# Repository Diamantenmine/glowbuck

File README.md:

# glowbuck
Glowbuck is a voltage converter and control board that allows you to power addressable LED strips with USB-C PD.

Together with [Firefly Luciferin](https://github.com/sblantipodi/firefly_luciferin), you can create your own ambilight that connects via USB-C to your computer and draws power from a USB-C PD power supply. Glowbuck is in no way associated with the linked project.

The left USB-C socket is used for data. The right socket shall be connected to a suitable USB-C PD supply. The spring-loaded connection terminal allows easy and safe connection to a 5 V addressable LED strip with, for example, SK6812 or WS2812B. The output current is measured with a 2 mOhm shunt. A shunt amplifier allows the integrated ESP32 S3 to measure the current flow and shut down the buck regulator when an unusually large current is detected.

## Quick Facts:
- Output: 5 V @ 10 A
- Input: 20 V @ 3 A. Via I2C, the microcontroller can reconfigure the PD controller and negotiate other voltage and current requirements for the input.
- Microcontroller: ESP32 S3
- Output current measurement with an integrated shunt

## Warning and Disclaimer

**Warning**: This project is in a alpha state and the hardware has not yet been tested.

This project is provided "as is" without warranty of any kind, either expressed or implied. The author makes no guarantees regarding the functionality, reliability, or suitability of this project for any particular purpose.
By using this project, you acknowledge and agree that:
- No liability is accepted for any damages, losses, or issues arising from the use or inability to use this project
- There is no guarantee that this project will work as intended or work at all
- The author shall not be held responsible for any direct, indirect, incidental, or consequential damages

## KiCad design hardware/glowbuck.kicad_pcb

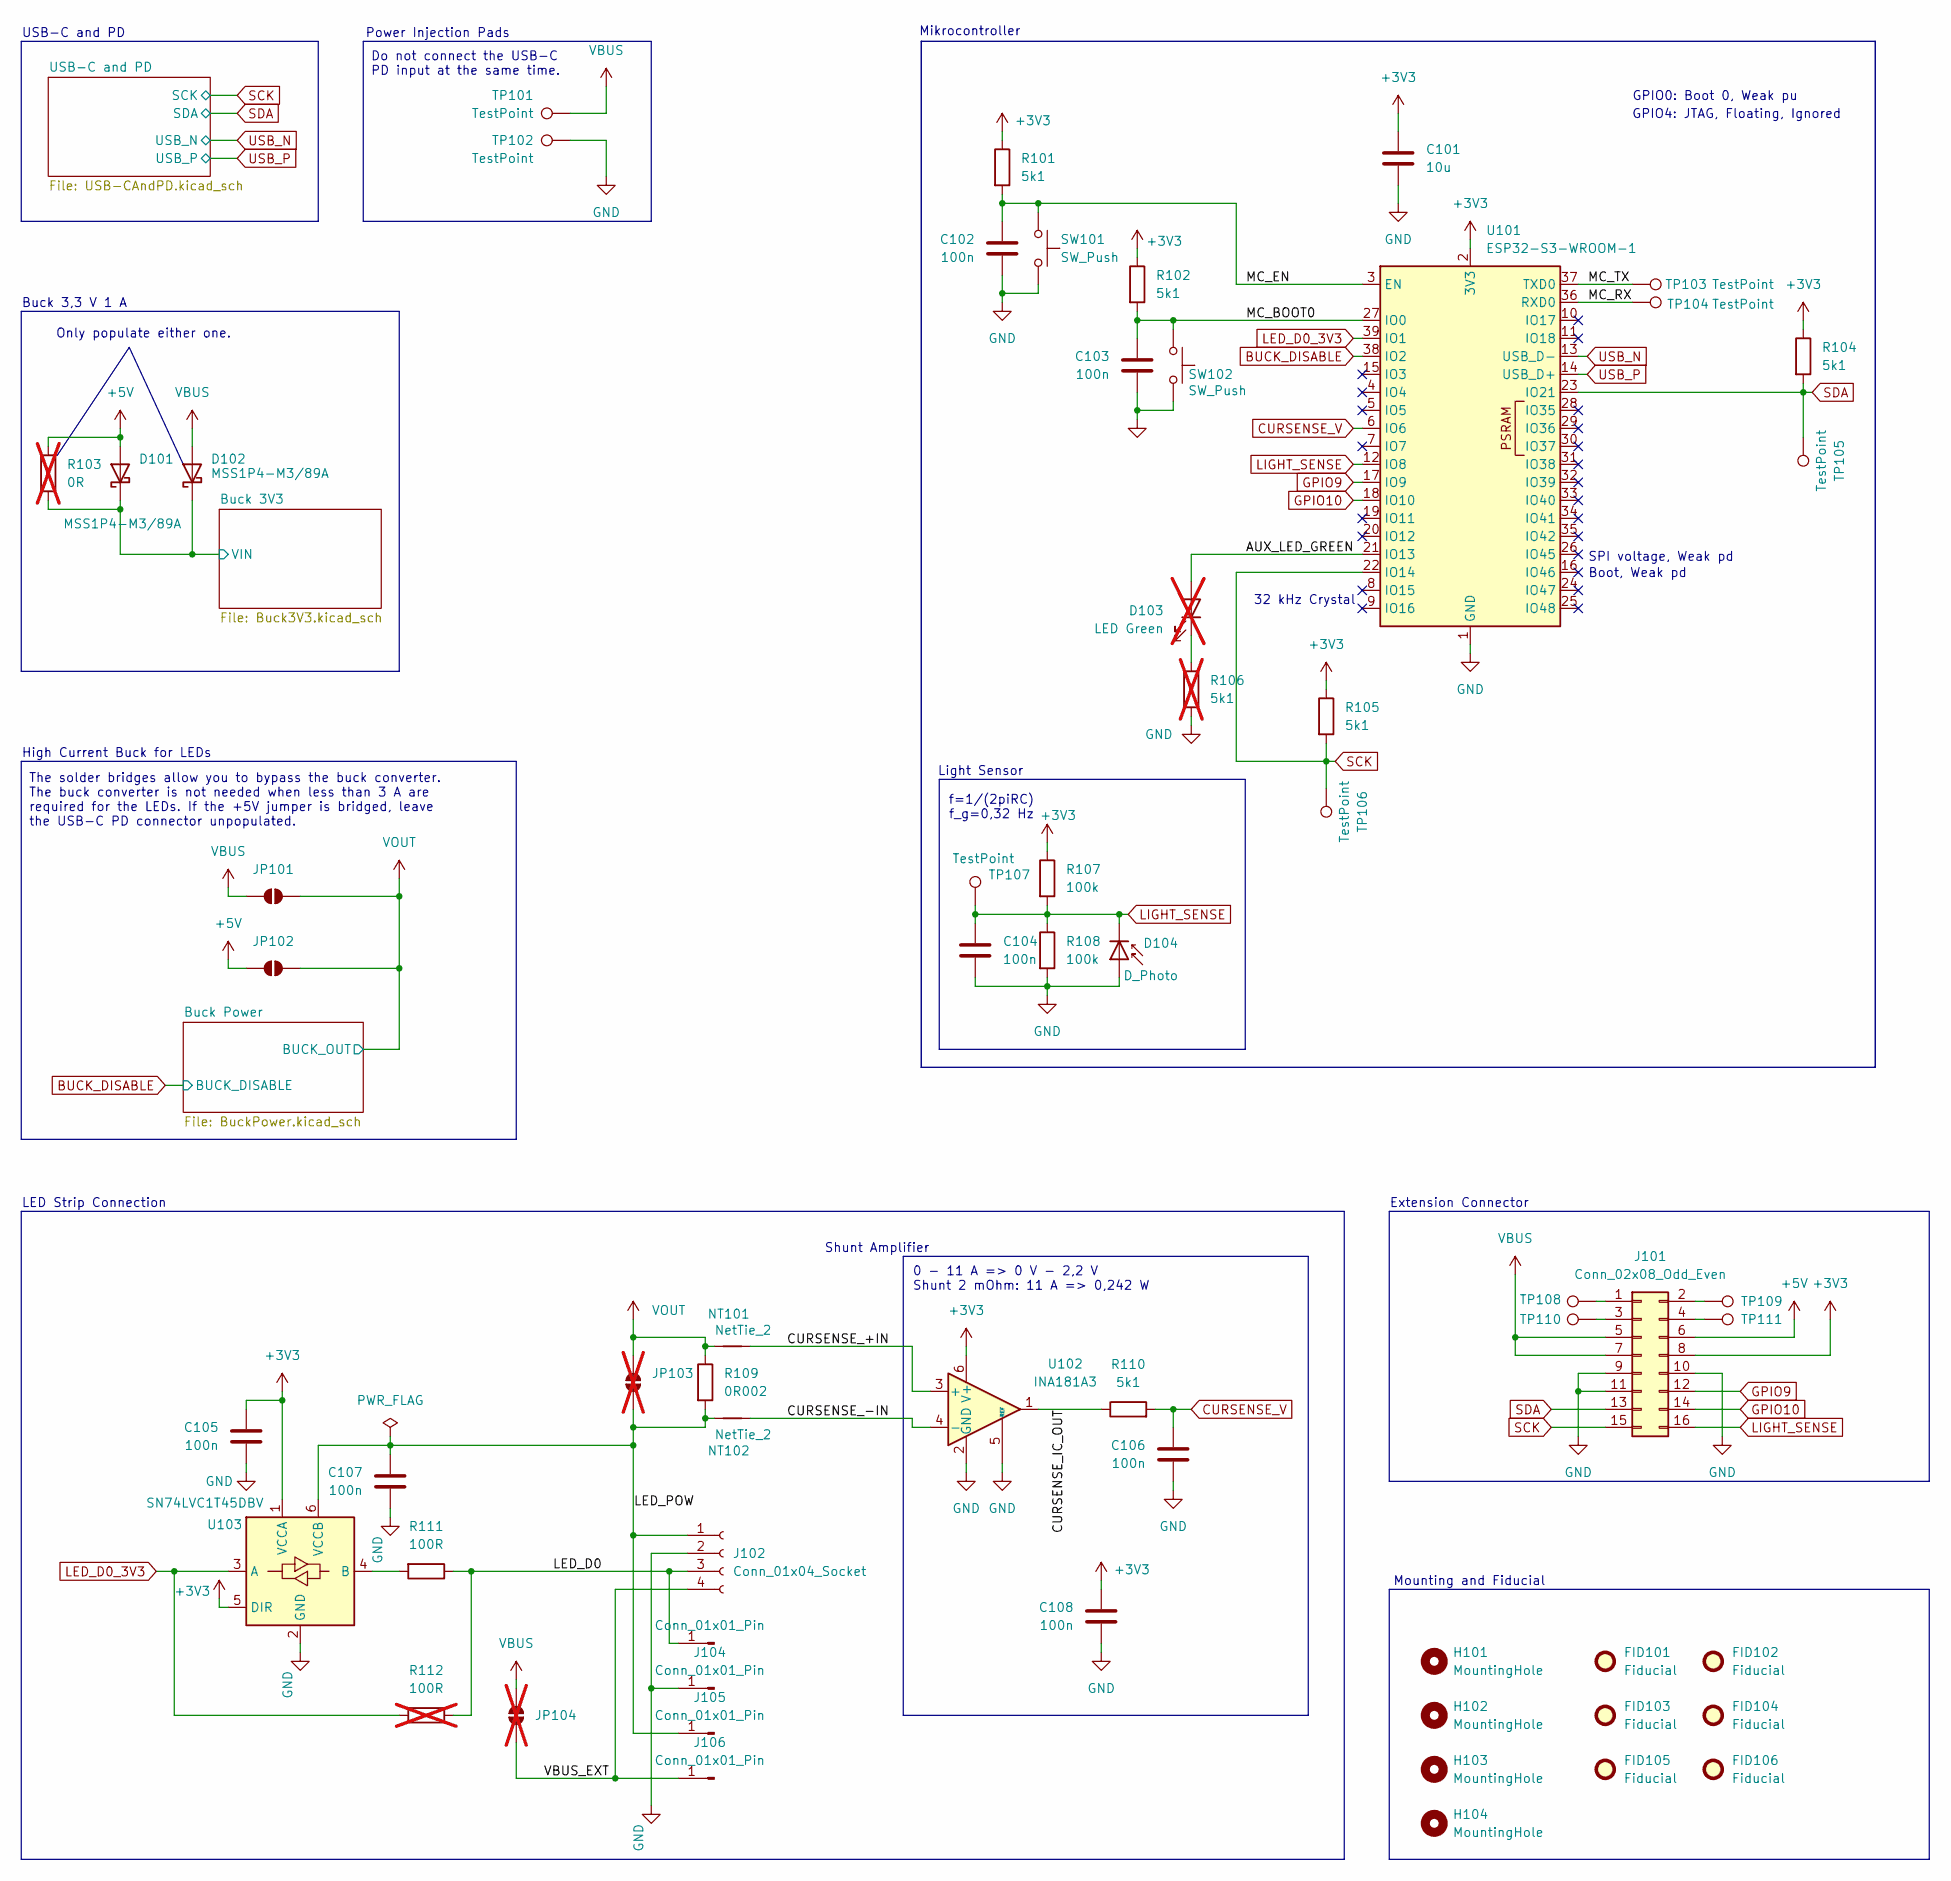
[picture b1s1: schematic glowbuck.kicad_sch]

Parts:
C101: 10u; C_0603_1608Metric; MouserNumber 187-CL10A106MA8NRNC
C102, C103, C104, C105, C106, C107, C108: 100n; C_0603_1608Metric; MouserNumber 187-CL10B104KB8WPND
D101, D102: MSS1P4-M3/89A; D_MicroSMP_AK; MouserNumber 625-MSS1P4-M3
D103: LED Green; LED_0603_1608Metric; MouserNumber 710-150060VS55040; not fitted
D104: D_Photo; D_1206_3216Metric; MouserNumber 743-IN-S126BTNPD
FID101, FID102, FID103, FID104, FID105, FID106: Fiducial; Fiducial_0.5mm_Mask1mm
H101, H102, H103, H104: MountingHole; MountingHole_2.2mm_M2_DIN965_Pad_TopBottom
J101: Conn_02x08_Odd_Even; PinHeader_2x08_P2.00mm_Vertical
J102: Conn_01x04_Socket; PTS 1,5_ 4-5,0-H; MouserNumber 651-1792889
J103: Conn_01x01_Pin; TestPoint_Pad_1.0x1.0mm
J104, J105, J106: Conn_01x01_Pin; TestPoint_Pad_3.0x3.0mm
JP101, JP102: SolderJumper_2_Open; SolderJumper_Open_HighCurrent
JP103, JP104: SolderJumper_2_Open; SolderJumper_Open_HighCurrent; not fitted
NT101, NT102: NetTie_2; NETTIE_0.3mm
R101, R102, R104, R105, R110: 5k1; R_0603_1608Metric; MouserNumber 603-RC0603FR-105K1L
R103: 0R; R_0603_1608Metric; MouserNumber 603-RC0603FR-130RL; not fitted
R106: 5k1; R_0603_1608Metric; MouserNumber 603-RC0603FR-105K1L; not fitted
R107, R108: 100k; R_0603_1608Metric; MouserNumber 603-RT0603FRE07100KL
R109: 0R002; R_0805_2012Metric; MouserNumber 71-WFC08052L000FE66
R111: 100R; R_0603_1608Metric; MouserNumber 603-RE0603FRE07100RL
R112: 100R; R_0603_1608Metric; MouserNumber 603-RE0603FRE07100RL; not fitted
SW101, SW102: SW_Push; PTS526_GPins_NoGround_2Pole; MouserNumber 611-PTS526SM20S21LFS
TP101, TP102: TestPoint; TestPoint_Pad_3.0x3.0mm
TP103, TP104, TP105, TP106, TP107, TP108, TP109, TP110, TP111: TestPoint; TestPoint_Pad_D1.0mm
U101: ESP32-S3-WROOM-1; MouserNumber 356-ESP32-S3WROOM1N4
U102: INA181A3; SOT-23-6; MouserNumber 595-INA181A3IDBVR
U103: SN74LVC1T45DBV; SOT-23-6; MouserNumber 595-74LVC1T45DBVRG4

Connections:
+3V3: C101.1, C105.1, C108.1, J101.8, R101.1, R102.1, R104.1, R105.1, R107.1, U101.2 (3V3), U102.6 (V+), U103.1 (VCCA), U103.5 (DIR); also elsewhere on the board
+5V: D101.2 (A), J101.6, JP102.1 (A), R103.2; also elsewhere on the board
/AUX_LED_GREEN: D103.2 (A), U101.21 (IO13)
/Buck 3V3/VIN: D101.1 (K), D102.1 (K), R103.1; also elsewhere on the board
/CURSENSE_+IN: NT101.1, U102.3 (+)
/CURSENSE_-IN: NT102.1, U102.4 (-)
/CURSENSE_IC_OUT: R110.1, U102.1
/LED_D0: J102.3, J103.1, R111.1, R112.1
/LED_POW: C107.1, J102.1, J105.1, JP103.1 (A), NT102.2, R109.2, U103.6 (VCCB)
/MC_BOOT0: C103.1, R102.2, SW102.1, U101.27 (IO0)
/MC_EN: C102.1, R101.2, SW101.1, U101.3 (EN)
/MC_RX: TP104.1, U101.36 (RXD0)
/MC_TX: TP103.1, U101.37 (TXD0)
/VBUS_EXT: J102.4, J106.1, JP104.1 (A)
BUCK_DISABLE: U101.38 (IO2); also elsewhere on the board
CURSENSE_V: C106.1, R110.2, U101.6 (IO6)
GND: C101.2, C102.2, C103.2, C104.2, C105.2, C106.2, C107.2, C108.2, D104.2 (A), J101.9, J101.10, J101.11, J102.2, J104.1, R106.2, R108.2, SW101.2, SW102.2, TP102.1, U101.1 (GND), U101.40 (GND), U101.41 (GND), U102.2 (GND), U102.5 (REF), U103.2 (GND); also elsewhere on the board
GPIO9: J101.12, U101.17 (IO9)
GPIO10: J101.14, U101.18 (IO10)
LED_D0_3V3: R112.2, U101.39 (IO1), U103.3 (A)
LIGHT_SENSE: C104.1, D104.1 (K), J101.16, R107.2, R108.1, TP107.1, U101.12 (IO8)
unnamed: D103.1 (K), R106.1
unnamed: J101.1, TP108.1
unnamed: J101.2, TP109.1
unnamed: J101.3, TP110.1
unnamed: J101.4, TP111.1
unnamed: R111.2, U103.4 (B)
SCK: J101.15, R105.2, TP106.1, U101.22 (IO14); also elsewhere on the board
SDA: J101.13, R104.2, TP105.1, U101.23 (IO21); also elsewhere on the board
USB_N: U101.13 (USB_D-); also elsewhere on the board
USB_P: U101.14 (USB_D+); also elsewhere on the board
VBUS: D102.2 (A), J101.5, J101.7, JP101.1 (A), JP104.2 (B), TP101.1; also elsewhere on the board
VOUT: JP101.2 (B), JP102.2 (B), JP103.2 (B), NT101.2, R109.1; also elsewhere on the board

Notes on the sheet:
Only populate either one.
SPI voltage, Weak pd
Do not connect the USB-C PD input at the same time.
Mikrocontroller
Light Sensor
Power Injection Pads
GPIO4: JTAG, Floating, Ignored
Buck 3,3 V 1 A
Mounting and Fiducial
0 - 11 A => 0 V - 2,2 V Shunt 2 mOhm: 11 A => 0,242 W
GPIO0: Boot 0, Weak pu
Extension Connector
USB-C and PD
Boot, Weak pd
Shunt Amplifier
The solder bridges allow you to bypass the buck converter. The buck converter is not needed when less than 3 A are required for the LEDs. If the +5V jumper is bridged, leave the USB-C PD connector unpopulated.
32 kHz Crystal
f=1/(2piRC) f_g=0,32 Hz
LED Strip Connection
High Current Buck for LEDs

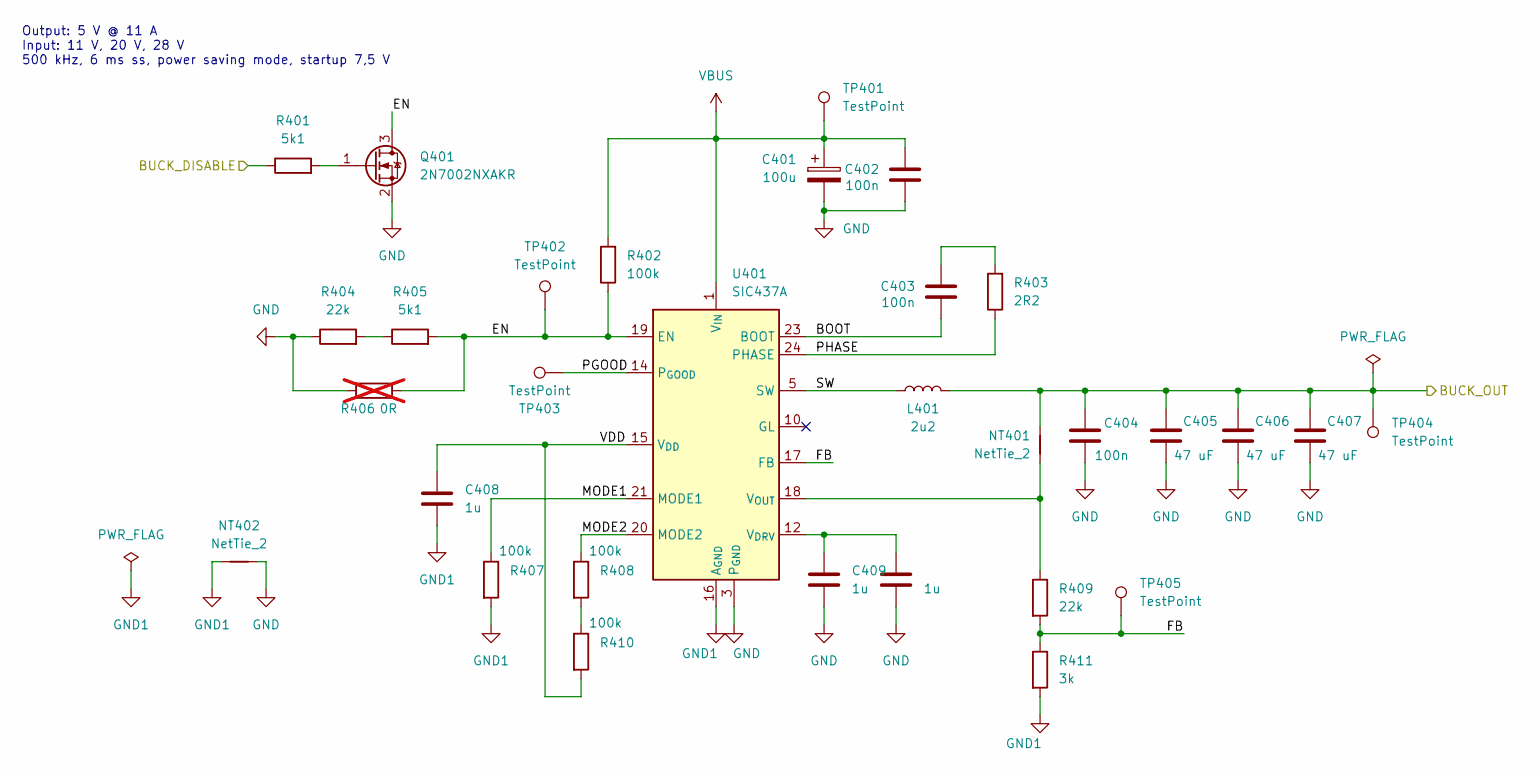
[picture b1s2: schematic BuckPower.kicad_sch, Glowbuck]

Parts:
C401: 100u; CP_Elec_8x10; MouserNumber 647-PCZ1V101MCL6GS
C402, C403, C404: 100n; C_0603_1608Metric; MouserNumber 187-CL10B104KB8WPND
C405, C406, C407: 47 uF; C_1210_3225Metric; MouserNumber 81-GRM32ER71A476KE5L
C408, C409, C410: 1u; C_0603_1608Metric; MouserNumber 187-CL10B105KA8NFNC
L401: 2u2; L_Vishay_IHLP-6767; MouserNumber 70-IHLP6767GZER2R2M0
NT401: NetTie_2; NETTIE_0.2mm
NT402: NetTie_2; NETTIE_0.3mm
Q401: 2N7002NXAKR; SOT-23-3; MouserNumber 771-2N7002NXAKR
R401, R405: 5k1; R_0603_1608Metric; MouserNumber 603-RC0603FR-105K1L
R402, R407, R408, R410: 100k; R_0603_1608Metric; MouserNumber 603-RT0603FRE07100KL
R403: 2R2; R_0603_1608Metric; MouserNumber 71-CRCW0603-2.2-E3
R404, R409: 22k; R_0603_1608Metric; MouserNumber 603-RT0603DRE0722KL
R406: 0R; R_0603_1608Metric; MouserNumber 603-RC0603FR-130RL; not fitted
R411: 3k; R_0603_1608Metric; MouserNumber 603-RC0603FR-133KL
TP401, TP402, TP403, TP404, TP405: TestPoint; TestPoint_Pad_D1.0mm
U401: SIC437A; Vishay_PowerPAK_MLP44-24L_ThermalVias; MouserNumber 78-SIC437AED-T1-GE3

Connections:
/Buck Power/BOOT: C403.2, U401.23 (BOOT)
/Buck Power/EN: Q401.3 (D), R402.1, R405.2, R406.1, TP402.1, U401.19 (EN)
/Buck Power/FB: R409.2, R411.1, TP405.1, U401.17 (FB)
/Buck Power/MODE1: R407.1, U401.21 (MODE1)
/Buck Power/MODE2: R408.1, U401.20 (MODE2)
/Buck Power/PGOOD: TP403.1, U401.14 (P_{GOOD})
/Buck Power/PHASE: R403.1, U401.24 (PHASE)
/Buck Power/SW: L401.1, U401.5 (SW), U401.6 (SW), U401.7 (SW), U401.8 (SW), U401.9 (SW)
/Buck Power/VDD: C408.1, R410.2, U401.15 (V_{DD})
BUCK_DISABLE: R401.1; also elsewhere on the board
GND: C401.2, C402.2, C404.2, C405.2, C406.2, C407.2, C409.1, C410.2, NT402.2, Q401.2 (S), R404.1, R406.2, U401.3 (P_{GND}), U401.4 (P_{GND}), U401.13 (P_{GND}), U401.27 (P_{GND}); also elsewhere on the board
GND1: C408.2, NT402.1, R407.2, R411.2, U401.16 (A_{GND}), U401.25 (A_{GND})
unnamed: C403.1, R403.2
unnamed: Q401.1 (G), R401.2
unnamed: R404.2, R405.1
unnamed: R408.2, R410.1
unnamed: C409.2, C410.1, U401.12 (V_{DRV})
unnamed: NT401.2, R409.1, U401.18 (V_{OUT})
VBUS: C401.1, C402.1, R402.2, TP401.1, U401.1 (V_{IN}), U401.2 (V_{IN}), U401.22 (V_{IN}), U401.26 (V_{IN}); also elsewhere on the board
VOUT: C404.1, C405.1, C406.1, C407.1, L401.2, NT401.1, TP404.1; also elsewhere on the board

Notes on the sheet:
Output: 5 V @ 11 A Input: 11 V, 20 V, 28 V 500 kHz, 6 ms ss, power saving mode, startup 7,5 V

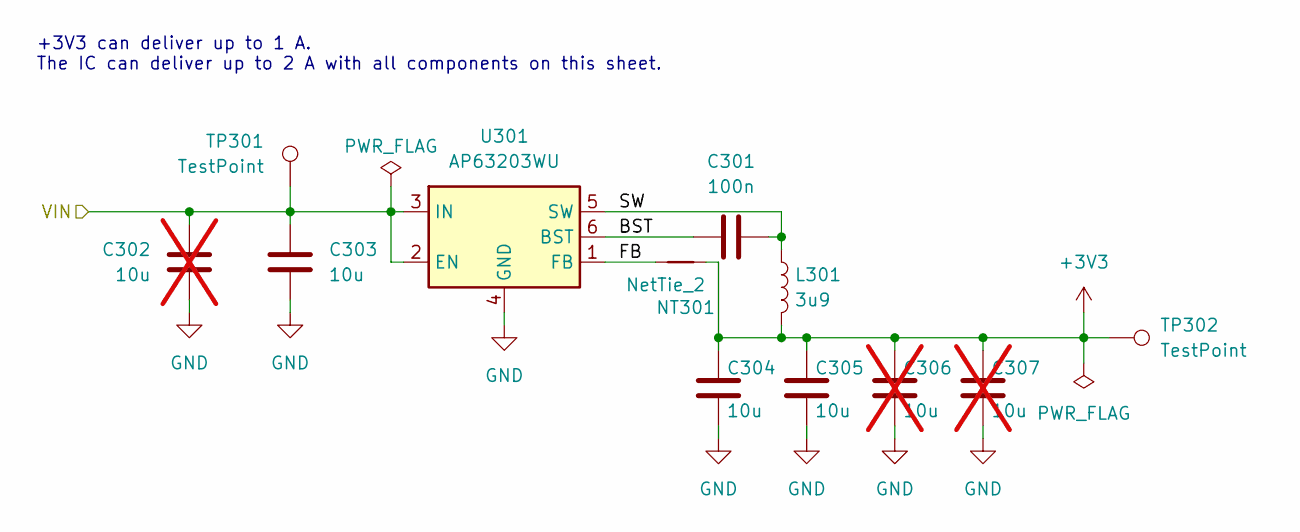
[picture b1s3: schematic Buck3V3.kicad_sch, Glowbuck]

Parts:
C301: 100n; C_0603_1608Metric; MouserNumber 187-CL10B104KB8WPND
C302: 10u; C_1210_3225Metric; MouserNumber 187-CL32B106KBJNNNE; not fitted
C303: 10u; C_1210_3225Metric; MouserNumber 187-CL32B106KBJNNNE
C304, C305: 10u; C_0603_1608Metric; MouserNumber 187-CL10A106MA8NRNC
C306, C307: 10u; C_0603_1608Metric; MouserNumber 187-CL10A106MA8NRNC; not fitted
L301: 3u9; BOURNS_SRR7045; MouserNumber 652-SRR7045-3R9M
NT301: NetTie_2; NETTIE_0.3mm
TP301, TP302: TestPoint; TestPoint_Pad_D1.5mm
U301: AP63203WU; TSOT-23-6; MouserNumber 621-AP63203WU-7

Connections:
+3V3: C304.2, C305.2, C306.2, C307.2, L301.2, NT301.2, TP302.1; also elsewhere on the board
/Buck 3V3/BST: C301.1, U301.6 (BST)
/Buck 3V3/FB: NT301.1, U301.1 (FB)
/Buck 3V3/SW: C301.2, L301.1, U301.5 (SW)
/Buck 3V3/VIN: C302.1, C303.2, TP301.1, U301.2 (EN), U301.3 (IN); also elsewhere on the board
GND: C302.2, C303.1, C304.1, C305.1, C306.1, C307.1, U301.4 (GND); also elsewhere on the board

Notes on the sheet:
+3V3 can deliver up to 1 A. The IC can deliver up to 2 A with all components on this sheet.

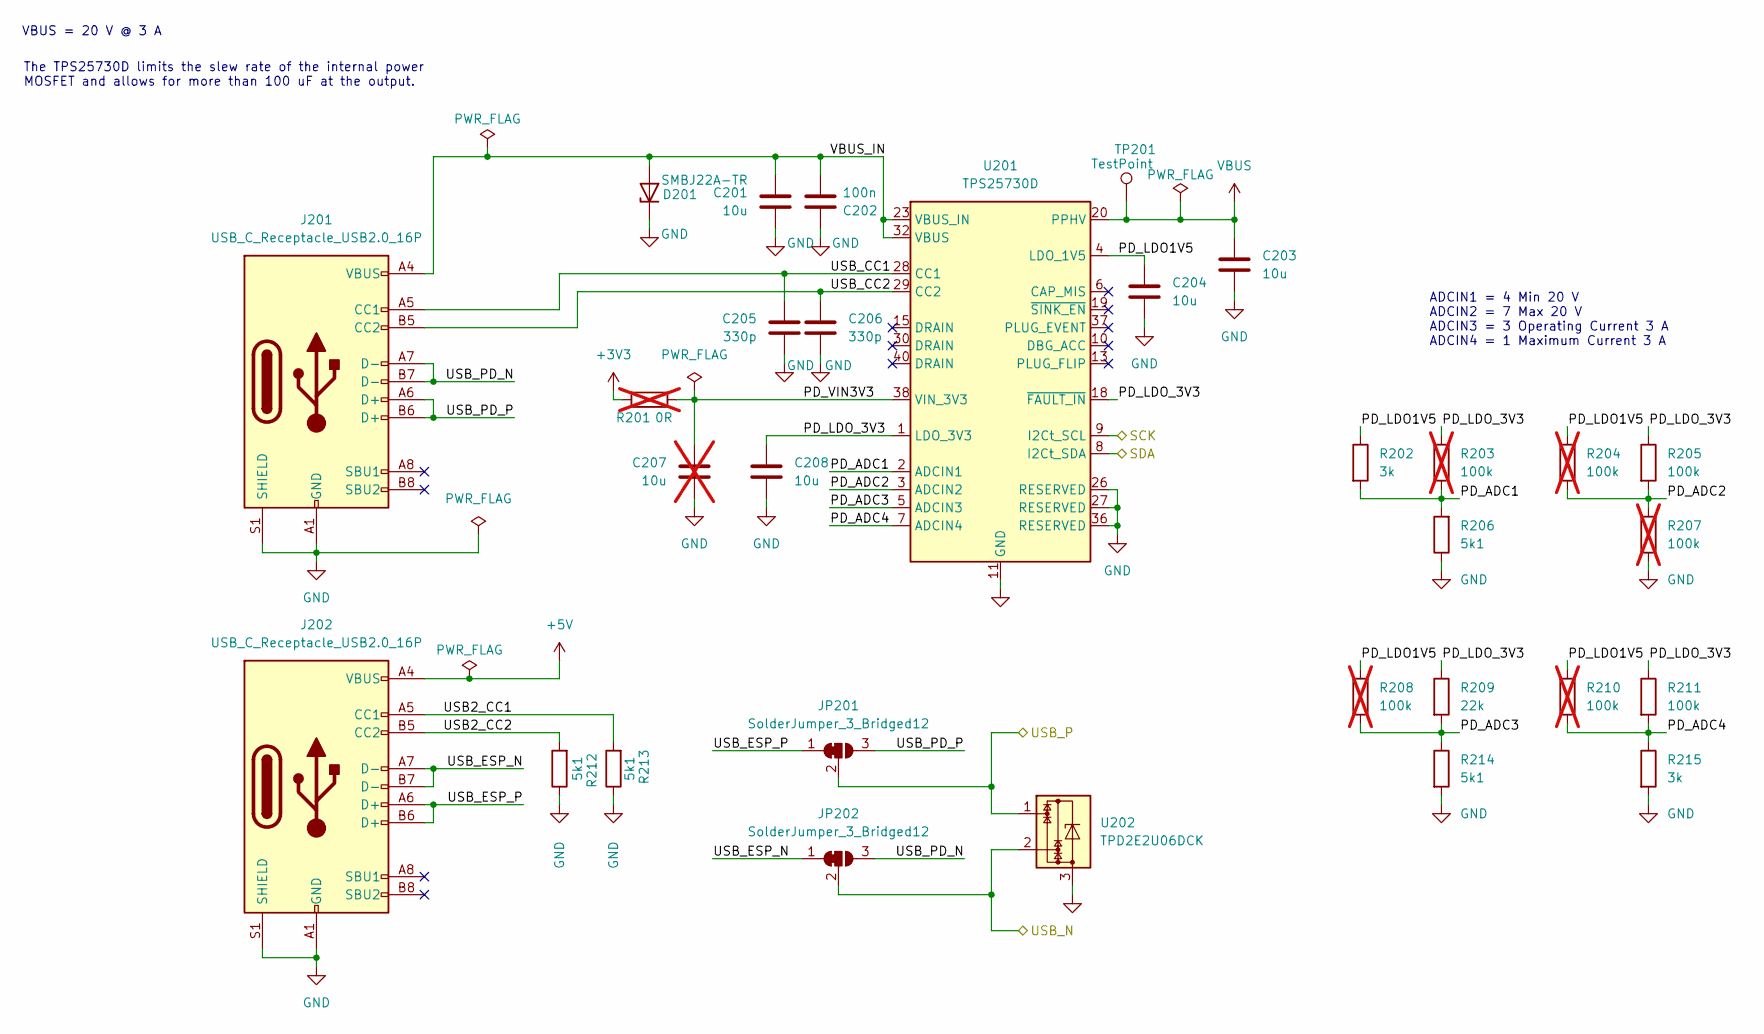
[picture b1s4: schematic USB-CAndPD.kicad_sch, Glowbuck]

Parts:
C201, C203: 10u; C_1210_3225Metric; MouserNumber 187-CL32B106KBJNNNE
C202: 100n; C_0603_1608Metric; MouserNumber 187-CL10B104KB8WPND
C204, C208: 10u; C_0603_1608Metric; MouserNumber 187-CL10A106MA8NRNC
C205, C206: 330p; C_0603_1608Metric; MouserNumber 80-C0603C331K5R
C207: 10u; C_0603_1608Metric; MouserNumber 187-CL10A106MA8NRNC; not fitted
D201: SMBJ22A-TR; D_SMB; MouserNumber 511-SMBJ22A
J201, J202: USB_C_Receptacle_USB2.0_16P; USB_C_Receptacle_GCT_USB4105-xx-A_16P_TopMnt_Horizontal; MouserNumber 640-USB4105-GF-A
JP201, JP202: SolderJumper_3_Bridged12; SolderJumper_123_0603
R201: 0R; R_0603_1608Metric; MouserNumber 603-RC0603FR-130RL; not fitted
R202, R215: 3k; R_0603_1608Metric; MouserNumber 603-RC0603FR-133KL
R203, R204, R207, R208, R210: 100k; R_0603_1608Metric; MouserNumber 603-RT0603FRE07100KL; not fitted
R205, R211: 100k; R_0603_1608Metric; MouserNumber 603-RT0603FRE07100KL
R206, R212, R213, R214: 5k1; R_0603_1608Metric; MouserNumber 603-RC0603FR-105K1L
R209: 22k; R_0603_1608Metric; MouserNumber 603-RT0603DRE0722KL
TP201: TestPoint; TestPoint_Pad_D1.5mm
U201: TPS25730D; Texas_REF0038A_WQFN-38-2EP_6x4mm_P0.4; MouserNumber 595-TPS25730DREFR
U202: TPD2E2U06DCK; SOT-323_SC-70; MouserNumber 595-TPD2E2U06QDCKRQ1

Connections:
+3V3: R201.2; also elsewhere on the board
+5V: J202.A4 (VBUS), J202.A9 (VBUS), J202.B4 (VBUS), J202.B9 (VBUS); also elsewhere on the board
/USB-C and PD/PD_ADC1: R202.2, R203.2, R206.2, U201.2 (ADCIN1)
/USB-C and PD/PD_ADC2: R204.2, R205.2, R207.1, U201.3 (ADCIN2)
/USB-C and PD/PD_ADC3: R208.2, R209.2, R214.1, U201.5 (ADCIN3)
/USB-C and PD/PD_ADC4: R210.2, R211.2, R215.1, U201.7 (ADCIN4)
/USB-C and PD/PD_LDO1V5: C204.2, R202.1, R204.1, R208.1, R210.1, U201.4 (LDO_1V5)
/USB-C and PD/PD_LDO_3V3: C208.2, R203.1, R205.1, R209.1, R211.1, U201.1 (LDO_3V3), U201.18 (~FAULT_IN)
/USB-C and PD/PD_VIN3V3: C207.2, R201.1, U201.38 (VIN_3V3)
/USB-C and PD/USB2_CC1: J202.A5 (CC1), R213.2
/USB-C and PD/USB2_CC2: J202.B5 (CC2), R212.2
/USB-C and PD/USB_CC1: C205.1, J201.A5 (CC1), U201.28 (CC1)
/USB-C and PD/USB_CC2: C206.1, J201.B5 (CC2), U201.29 (CC2)
/USB-C and PD/USB_ESP_N: J202.A7 (D-), J202.B7 (D-), JP202.1 (A)
/USB-C and PD/USB_ESP_P: J202.A6 (D+), J202.B6 (D+), JP201.1 (A)
/USB-C and PD/USB_PD_N: J201.A7 (D-), J201.B7 (D-), JP202.3 (B)
/USB-C and PD/USB_PD_P: J201.A6 (D+), J201.B6 (D+), JP201.3 (B)
/USB-C and PD/VBUS_IN: C201.2, C202.2, D201.2 (A), J201.A4 (VBUS), J201.A9 (VBUS), J201.B4 (VBUS), J201.B9 (VBUS), U201.23 (VBUS_IN), U201.32 (VBUS)
GND: C201.1, C202.1, C203.1, C204.1, C205.2, C206.2, C207.1, C208.1, D201.1 (K), J201.A1 (GND), J201.A12 (GND), J201.B1 (GND), J201.B12 (GND), J201.S1 (SHIELD), J202.A1 (GND), J202.A12 (GND), J202.B1 (GND), J202.B12 (GND), J202.S1 (SHIELD), R206.1, R207.2, R212.1, R213.1, R214.2, R215.2, U201.11 (GND), U201.12 (GND), U201.14 (GND), U201.16 (GND), U201.17 (GND), U201.26 (RESERVED), U201.27 (RESERVED), U201.31 (GND), U201.34 (GND), U201.36 (RESERVED), U201.39 (GND), U202.3; also elsewhere on the board
SCK: U201.9 (I2Ct_SCL); also elsewhere on the board
SDA: U201.8 (I2Ct_SDA); also elsewhere on the board
USB_N: JP202.2 (C), U202.2; also elsewhere on the board
USB_P: JP201.2 (C), U202.1; also elsewhere on the board
VBUS: C203.2, TP201.1, U201.20 (PPHV); also elsewhere on the board

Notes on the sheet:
The TPS25730D limits the slew rate of the internal power MOSFET and allows for more than 100 uF at the output.
ADCIN1 = 4 Min 20 V ADCIN2 = 7 Max 20 V ADCIN3 = 3 Operating Current 3 A ADCIN4 = 1 Maximum Current 3 A
VBUS = 20 V @ 3 A

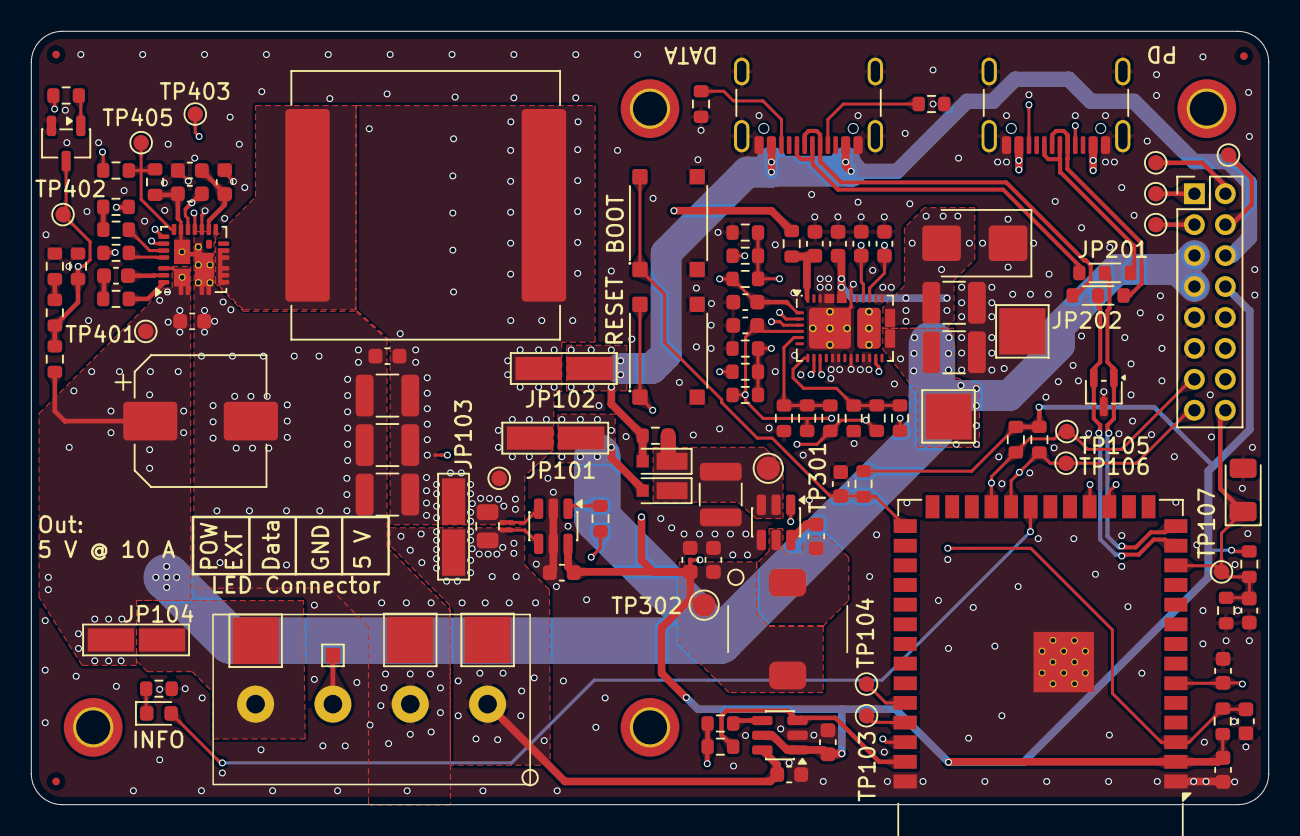
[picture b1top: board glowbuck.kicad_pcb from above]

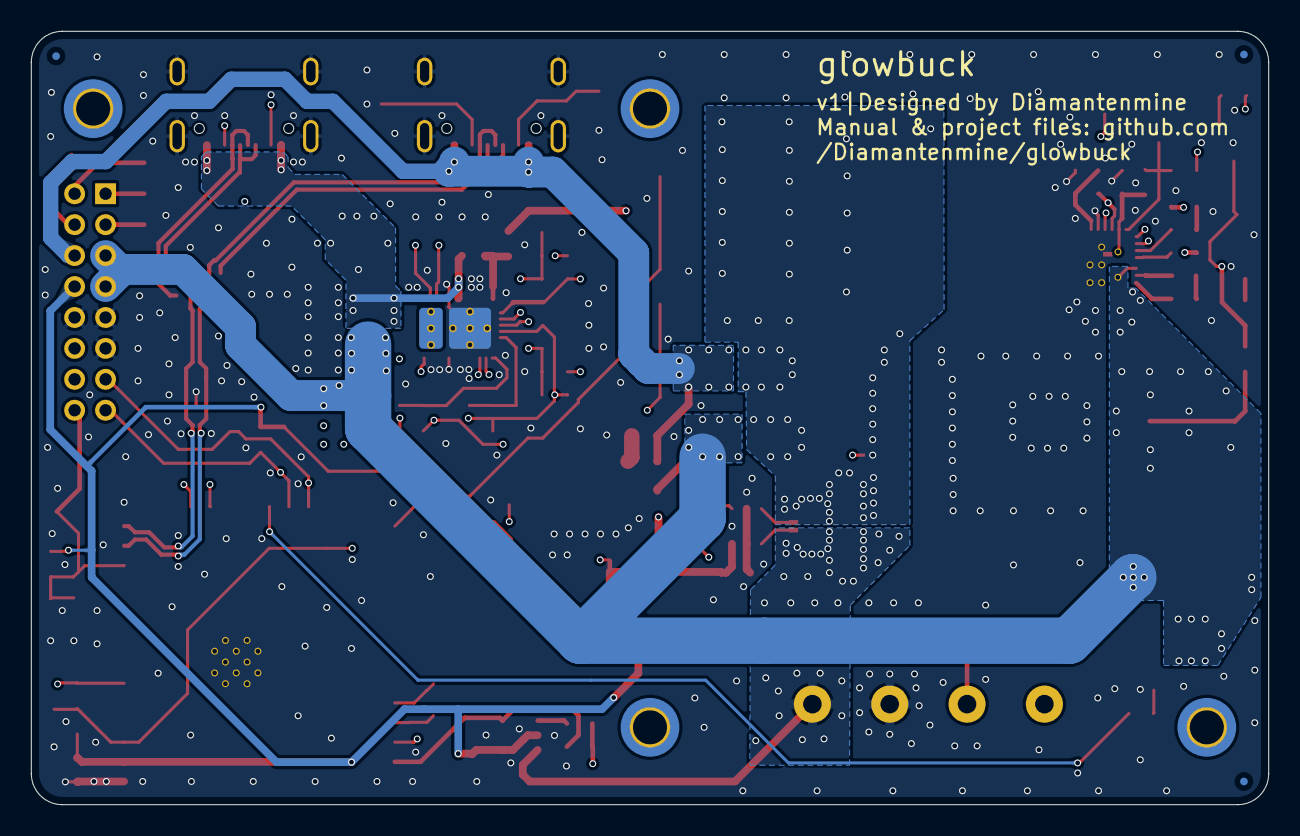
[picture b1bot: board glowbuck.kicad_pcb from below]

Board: 4 copper layers, 80.0 x 50.0 mm, 132 parts (3 on the bottom side), 68 nets.

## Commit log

2026-01-08 Schaltplan erstellt
2026-01-12 Optimized BOM and added netties
2026-01-14 Spring terminal, finalising PD settings, checking buck 10 A
2026-01-14 Changed footprints to non hand solder option
2026-01-17 Colored nets and added optional current measurement
2026-01-18 Set up PCB setting
2026-01-18 Global labels, explanation texts, fix spring connector
2026-01-21 Layout Stecker final, USB done, buck wip
2026-01-25 Layout in progress. I2C done
2026-01-27 Fixed drc errors
2026-01-31 Fixed drc problems
2026-01-31 Exchanged shunt resistor
2026-01-31 Added ManufacturerNumber for every item and fixed bom errors
2026-01-31 Connected VBUS to the free phoenix connector pin
2026-01-31 Thermal reliefes
2026-01-31 Exchanged 5k11 with 5k1 part number
2026-01-31 Expand README with project details and disclaimers
    Added detailed project description, specifications, and warnings.
2026-01-31 Adjusted product numbers and silkscreen for ordernumber
2026-01-31 Teardrops
2026-02-01 Optimized via silkscreen overlap and added pdf circuit diagram
